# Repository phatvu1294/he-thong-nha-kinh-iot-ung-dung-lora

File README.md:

# Hệ thống nhà kính IO ứng dụng LoRa
*Hệ thống nhà kính IOT ứng dựng LoRa được phát triển dựa trên ESP32, Arduino, LoRa, MQTT, Nodejs và C# Winform*

### Giới thiệu
Đây là một dự án hoàn toàn mới tại Việt Nam, việc áp dụng IOT và công nghệ LoRa đã mở ra một bước đi mới trong nghành nông nghiệp. Đi đôi với cuộc cách mạng công nghệ 4.0, IOT là một phần thiết yếu để phát triển nông nghiệp. Với việc gần như được áp dụng vào thực tế, càng chứng tỏ đây chính là một dự án cấp thiết, việc nghiên cứu và phát triển thêm sẽ càng giúp cho đất nước chúng ta hội nhập và phát triển hơn nữa.

### Mô hình

Mô hình lấy Gateway làm trung tâm để xây dựng, Gateway được xây dựng bằng module ESP32, module LoRa Ra-01 và OLED, có nhiệm vụ là chờ tiếp nhận dữ liệu LoRa từ các Node cảm biến (Node CO2, Node Temp, Node Light), xử lý hiển thị OLED và publish chúng lên broker, sau đó được đẩy lên Server hoặc phần mềm điều khiển (C# Winform).

Node cảm biển, cụ thể ở đây là Node CO2 được xây dựng bằng vi điều khiển ATMega328, module LoRa Ra-01, OLED và cảm biến COZIR-AX-5000. Nhiệm vụ là đọc giá trị CO2 và truyền dữ liệu LoRa tới Gateway.

Gateway kết nối với Server hoặc phần mềm thông qua phương thức MQTT, đây là phương thức truyền nhanh, với tốc độ băng thông thấp, … Chúng có dạng publish/subscribe. Khi nhận được dữ liệu LoRa từ Node cảm biến. Gateway xử lý dữ liệu và publish lên broker một message thông qua một topic, lúc này Server hoặc phần mềm sẽ subscribe topic đó và lắng nghe liên tục message từ topic đó, chỉ cần có một dữ liệu gửi lên từ Gateway, lập tức Server và phần mềm sẽ cập nhật giá trị mới theo message đã nhận được, ngược lại, khi Server hoặc Gateway publish dữ liệu, Gateway sẽ subscribe và lắng nghe chúng, nếu có message gửi về từ Server hoặc phần mềm, lập tức Gateway nhận được và chuyển thành dữ liệu LoRa và truyền đi tức thời tới Node điều khiển (Node Relay).

Server được xây dựng trên nền tảng Node.js và phần mềm được xây dựng trên nền tảng C# .NET. Tất cả chúng đều đã có thư viện MQTT hỗ trợ, việc còn lại là do người lập trình sáng tạo chúng như thế nào mà thôi.

### Gateway

Gateway được xây dựng với hạt nhân là module ESP32 và module LoRa Ra-01. Module ESP32 sử dụng chip 32 bit lõi kép cho phép xử lý dữ liệu tốc độ cao, ổn định. Module LoRa Ra-01 sử dụng chip SX1278 hỗ trợ truyền không dây RF lên tận hàng Km.

### Node CO2

Node CO2 được xây dựng với vđk ATMega328 (Arduino), module LoRa Ra-01 và cảm biến COZIR-AX-5000. Cảm biến COZIR là cảm biến số cho phép đọc giá trị CO2 trực tiếp thông qua UART mà không cần phải tính toán gì nhiều.

### Server Nodejs

Server được xây dựng dựa trên nền tảng Node.js. Với việc sử dụng Socket.io cho phép Server hoạt động thời gian thực. Hệ thống đưa ra khuyến nghị ứng với từng giá trị. Ngoài ra còn có trang dự báo thời tiết cho phép xem tình hình thời tiết trong những ngày sắp tới.

### Phần mềm Winform

Phần mềm được xây dựng dựa trên nền tảng C# .NET. Hỗ trợ nhật ký cho phép người sử dụng theo dõi được sự thay đổi tức thời của các giá trị.

### Video demo hệ thống

[https://www.youtube.com/watch?v=TktAAO-llQs](https://www.youtube.com/watch?v=TktAAO-llQs)

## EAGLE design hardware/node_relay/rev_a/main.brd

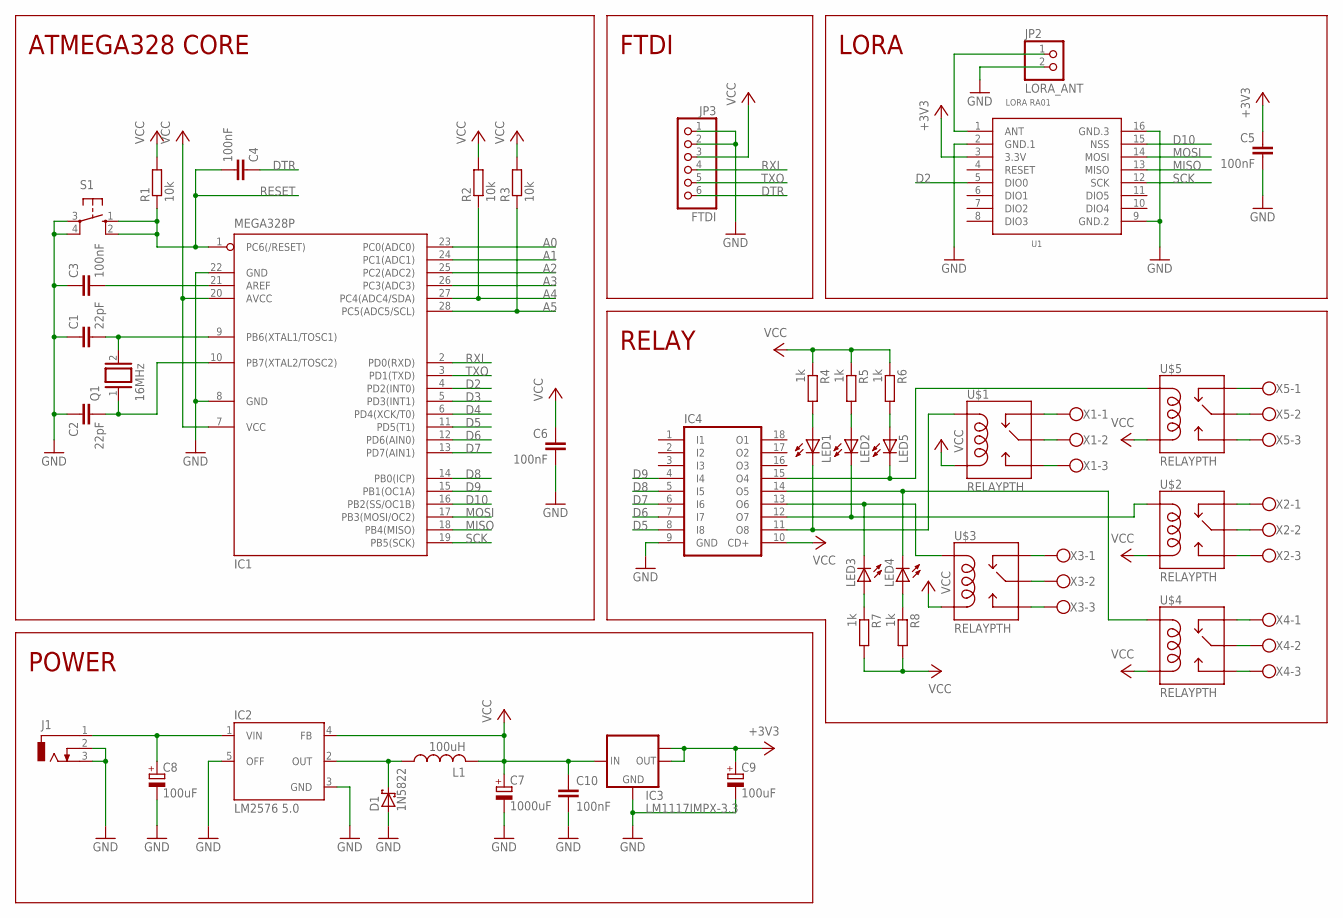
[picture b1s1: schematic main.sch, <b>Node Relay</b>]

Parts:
C1, C2: 22pF; C050-024X044
C3, C4, C5, C6, C10: 100nF; C050-024X044
C7: 1000uF; E5-13
C8: 100uF; E5-8,5
C9: 100uF; E3,5-10
D1: 1N5822; DO201T15
IC1: MEGA328P; DIL28-3
IC2: LM2576 5.0; TO263-5
IC3: LM1117IMPX-3.3; SOT223
IC4: ULN2803A; DIL18
J1: DCJ0303
JP2: LORA_ANT; 1X02
JP3: FTDI; 1X06
L1: 100uH; 6000-XXXX-RC
LED1, LED2, LED3, LED4, LED5: LED3MM
Q1: 16MHz; QS
R1, R2, R3: 10k; 0207/10
R4, R5, R6, R7, R8: 1k; 0207/10
S1: 10-XX; B3F-10XX
U1: LORA RA01; LORA-RA1-SMD
U$1, U$2, U$3, U$4, U$5: RELAYPTH; SRD-05VDC-SL-C
X1, X2, X3, X4, X5: W237-103

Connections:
+3V3: C5.1, C9.+, IC3.2 (OUT), IC3.TAB (OUT1), U1.3 (3.3V)
A0: IC1.23 (PC0(ADC0))
A1: IC1.24 (PC1(ADC1))
A2: IC1.25 (PC2(ADC2))
A3: IC1.26 (PC3(ADC3))
A4: IC1.27 (PC4(ADC4/SDA)), R2.1
A5: IC1.28 (PC5(ADC5/SCL)), R3.1
D2: IC1.4 (PD2(INT0)), U1.5 (DIO0)
D3: IC1.5 (PD3(INT1))
D4: IC1.6 (PD4(XCK/T0))
D5: IC1.11 (PD5(T1)), IC4.8 (I8)
D6: IC1.12 (PD6(AIN0)), IC4.7 (I7)
D7: IC1.13 (PD7(AIN1)), IC4.6 (I6)
D8: IC1.14 (PB0(ICP)), IC4.5 (I5)
D9: IC1.15 (PB1(OC1A)), IC4.4 (I4)
D10: IC1.16 (PB2(SS/OC1B)), U1.15 (NSS)
DTR: C4.1, JP3.6
GND: C1.1, C2.1, C3.1, C5.2, C6.2, C7.-, C8.-, C9.-, C10.2, D1.A, IC1.8 (GND), IC1.22 (GND), IC2.3 (GND), IC2.5 (OFF), IC3.1 (GND), IC4.9 (GND), J1.2, J1.3, JP2.2, JP3.1, JP3.2, S1.3, S1.4 (P1), U1.2 (GND.1), U1.9 (GND.2), U1.16 (GND.3)
MISO: IC1.18 (PB4(MISO)), U1.13 (MISO)
MOSI: IC1.17 (PB3(MOSI/OC2)), U1.14 (MOSI)
unnamed: JP2.1, U1.1 (ANT)
unnamed: C1.2, IC1.9 (PB6(XTAL1/TOSC1)), Q1.2
unnamed: C2.2, IC1.10 (PB7(XTAL2/TOSC2)), Q1.1
unnamed: C3.2, IC1.21 (AREF)
unnamed: C8.+, IC2.1 (VIN), J1.1
unnamed: D1.C, IC2.2 (OUT), L1.1
unnamed: U$1.SWCLOSED (SWCLOSE), X1.1
unnamed: U$1.SWCOMMON, X1.2
unnamed: U$1.SWOPEN, X1.3
unnamed: U$3.SWCOMMON, X3.2
unnamed: U$3.SWCLOSED (SWCLOSE), X3.1
unnamed: U$3.SWOPEN, X3.3
unnamed: U$4.SWCLOSED (SWCLOSE), X4.1
unnamed: U$4.SWCOMMON, X4.2
unnamed: U$4.SWOPEN, X4.3
unnamed: U$2.SWOPEN, X2.3
unnamed: U$2.SWCLOSED (SWCLOSE), X2.1
unnamed: U$2.SWCOMMON, X2.2
unnamed: IC4.11 (O8), LED1.K (C), U$1.COIL1
unnamed: IC4.12 (O7), LED2.K (C), U$2.COIL1
unnamed: IC4.13 (O6), LED3.K (C), U$3.COIL1
unnamed: IC4.14 (O5), LED4.K (C), U$4.COIL1
unnamed: U$5.SWCLOSED (SWCLOSE), X5.1
unnamed: U$5.SWOPEN, X5.3
unnamed: U$5.SWCOMMON, X5.2
unnamed: IC4.15 (O4), LED5.K (C), U$5.COIL1
unnamed: LED1.A, R4.2
unnamed: LED2.A, R5.2
unnamed: LED5.A, R6.2
unnamed: LED3.A, R7.1
unnamed: LED4.A, R8.1
RESET: C4.2, IC1.1 (PC6(/RESET)), R1.1, S1.1 (S), S1.2 (S1)
RXI: IC1.2 (PD0(RXD)), JP3.4
SCK: IC1.19 (PB5(SCK)), U1.12 (SCK)
TXO: IC1.3 (PD1(TXD)), JP3.5
VCC: C6.1, C7.+, C10.1, IC1.7 (VCC), IC1.20 (AVCC), IC2.4 (FB), IC3.3 (IN), IC4.10 (CD+), JP3.3, L1.2, R1.2, R2.2, R3.2, R4.1, R5.1, R6.1, R7.2, R8.2, U$1.COIL0, U$2.COIL0, U$3.COIL0, U$4.COIL0, U$5.COIL0

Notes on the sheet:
LORA
ATMEGA328 CORE
FTDI
POWER
RELAY

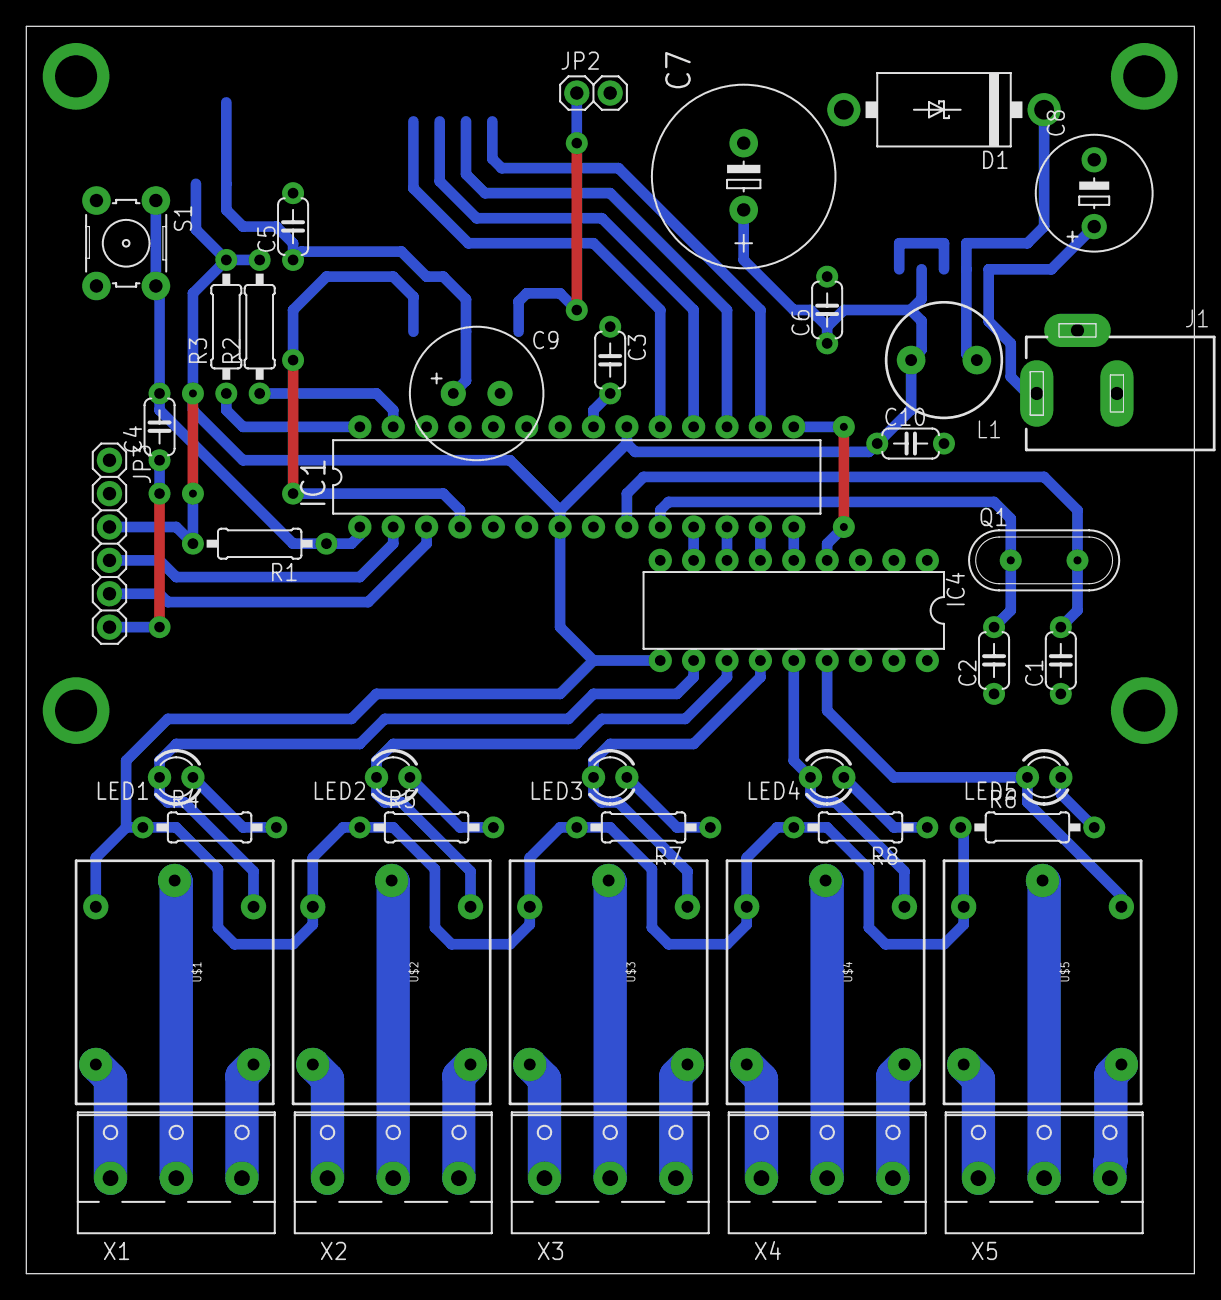
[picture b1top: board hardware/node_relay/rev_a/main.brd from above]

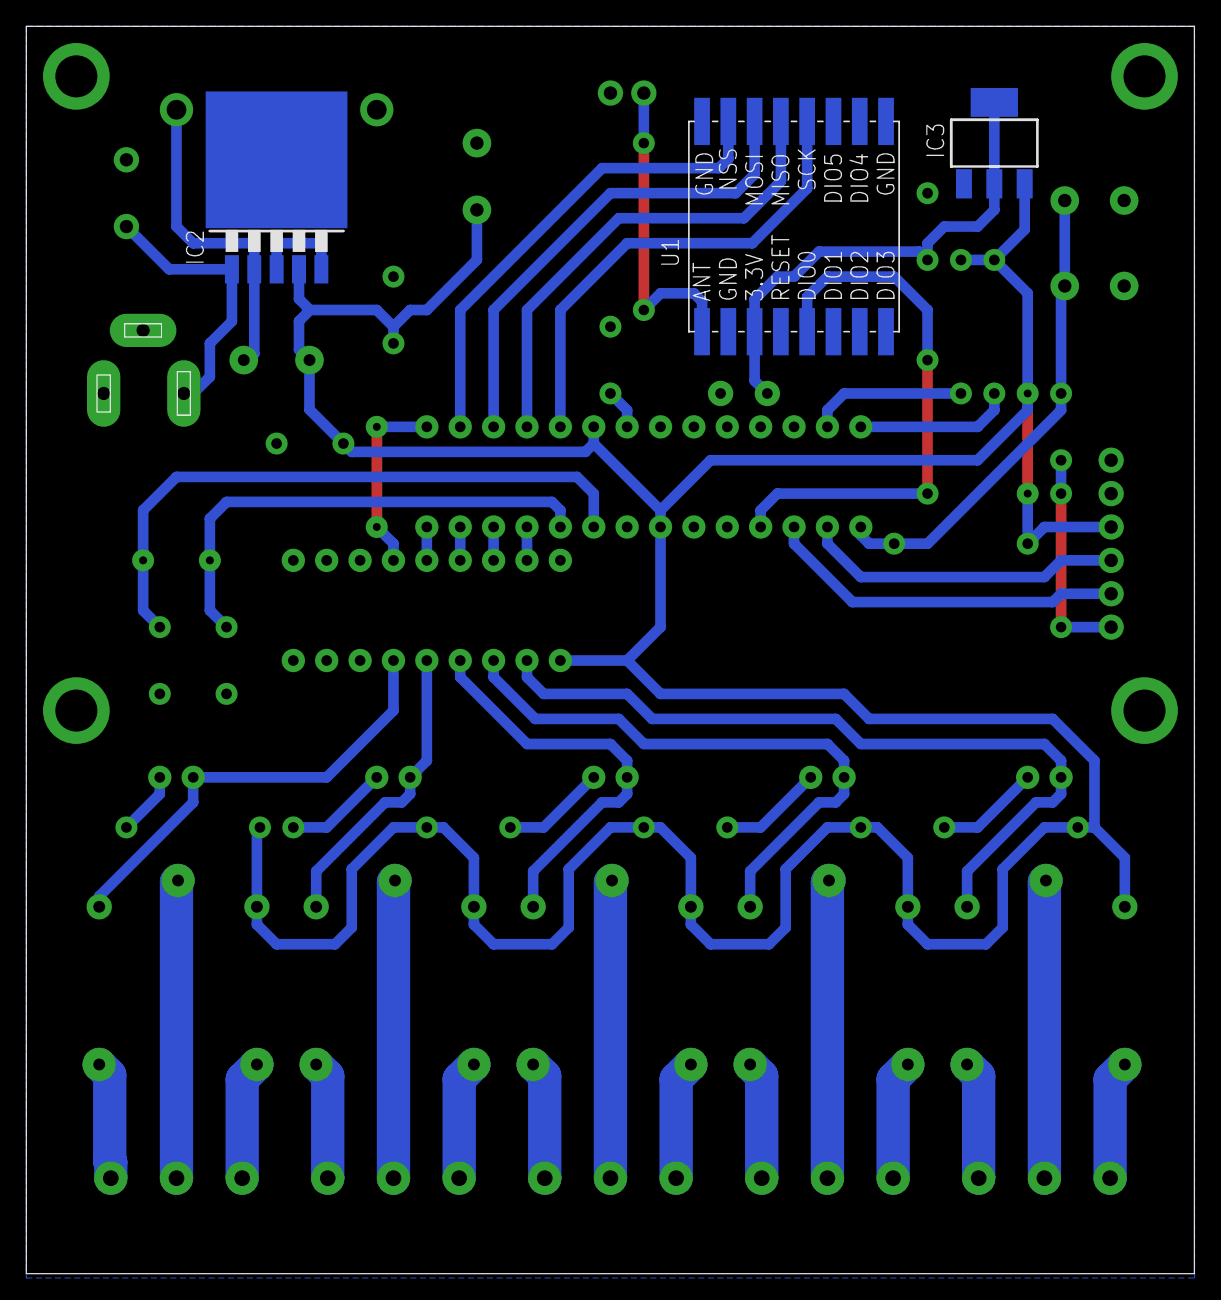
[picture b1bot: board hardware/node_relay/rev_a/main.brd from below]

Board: 2 copper layers, 88.9 x 94.9 mm, 45 parts (3 on the bottom side), 50 nets.

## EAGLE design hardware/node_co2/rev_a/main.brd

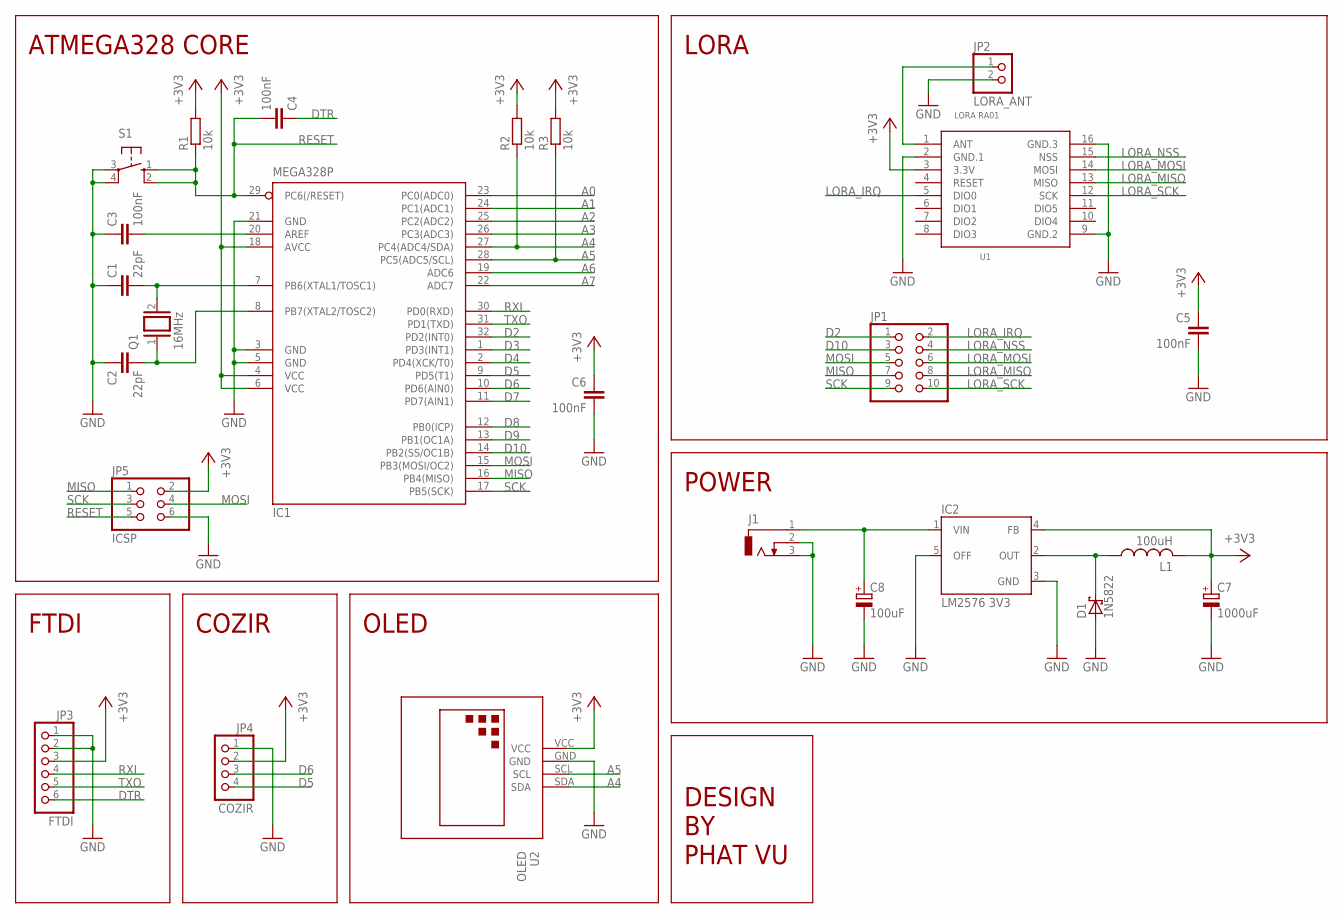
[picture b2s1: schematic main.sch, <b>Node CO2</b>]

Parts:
C1, C2: 22pF; C050-024X044
C3, C4, C5, C6: 100nF; C050-024X044
C7: 1000uF; E5-13
C8: 100uF; E5-8,5
D1: 1N5822; DO201T15
IC1: MEGA328P; TQFP32-08
IC2: LM2576 3V3; TO263-5
J1: DCJ0303
JP1: PINHD-2X5; 2X05
JP2: LORA_ANT; 1X02
JP3: FTDI; 1X06
JP4: COZIR; 1X04
JP5: ICSP; 2X03
L1: 100uH; 6000-XXXX-RC
Q1: 16MHz; QS
R1, R2, R3: 10k; 0207/10
S1: 10-XX; B3F-10XX
U1: LORA RA01; LORA-RA1-SMD
U2: OLED; OLED-096-I2C

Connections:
+3V3: C5.1, C6.1, C7.+, IC1.4 (VCC), IC1.6 (VCC), IC1.18 (AVCC), IC2.4 (FB), JP3.3, JP4.2, JP5.2, L1.2, R1.2, R2.2, R3.2, U1.3 (3.3V), U2.VCC
A0: IC1.23 (PC0(ADC0))
A1: IC1.24 (PC1(ADC1))
A2: IC1.25 (PC2(ADC2))
A3: IC1.26 (PC3(ADC3))
A4: IC1.27 (PC4(ADC4/SDA)), R2.1, U2.SDA
A5: IC1.28 (PC5(ADC5/SCL)), R3.1, U2.SCL
A6: IC1.19 (ADC6)
A7: IC1.22 (ADC7)
D2: IC1.32 (PD2(INT0)), JP1.1
D3: IC1.1 (PD3(INT1))
D4: IC1.2 (PD4(XCK/T0))
D5: IC1.9 (PD5(T1)), JP4.4
D6: IC1.10 (PD6(AIN0)), JP4.3
D7: IC1.11 (PD7(AIN1))
D8: IC1.12 (PB0(ICP))
D9: IC1.13 (PB1(OC1A))
D10: IC1.14 (PB2(SS/OC1B)), JP1.3
DTR: C4.1, JP3.6
GND: C1.1, C2.1, C3.1, C5.2, C6.2, C7.-, C8.-, D1.A, IC1.3 (GND), IC1.5 (GND), IC1.21 (GND), IC2.3 (GND), IC2.5 (OFF), J1.2, J1.3, JP2.2, JP3.1, JP3.2, JP4.1, JP5.6, S1.3, S1.4 (P1), U1.2 (GND.1), U1.9 (GND.2), U1.16 (GND.3), U2.GND
LORA_IRQ: JP1.2, U1.5 (DIO0)
LORA_MISO: JP1.8, U1.13 (MISO)
LORA_MOSI: JP1.6, U1.14 (MOSI)
LORA_NSS: JP1.4, U1.15 (NSS)
LORA_SCK: JP1.10, U1.12 (SCK)
MISO: IC1.16 (PB4(MISO)), JP1.7, JP5.1
MOSI: IC1.15 (PB3(MOSI/OC2)), JP1.5, JP5.4
unnamed: JP2.1, U1.1 (ANT)
unnamed: C1.2, IC1.7 (PB6(XTAL1/TOSC1)), Q1.2
unnamed: C2.2, IC1.8 (PB7(XTAL2/TOSC2)), Q1.1
unnamed: C3.2, IC1.20 (AREF)
unnamed: C8.+, IC2.1 (VIN), J1.1
unnamed: D1.C, IC2.2 (OUT), L1.1
RESET: C4.2, IC1.29 (PC6(/RESET)), JP5.5, R1.1, S1.1 (S), S1.2 (S1)
RXI: IC1.30 (PD0(RXD)), JP3.4
SCK: IC1.17 (PB5(SCK)), JP1.9, JP5.3
TXO: IC1.31 (PD1(TXD)), JP3.5

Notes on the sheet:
LORA
ATMEGA328 CORE
FTDI
COZIR
OLED
POWER
DESIGN BY PHAT VU

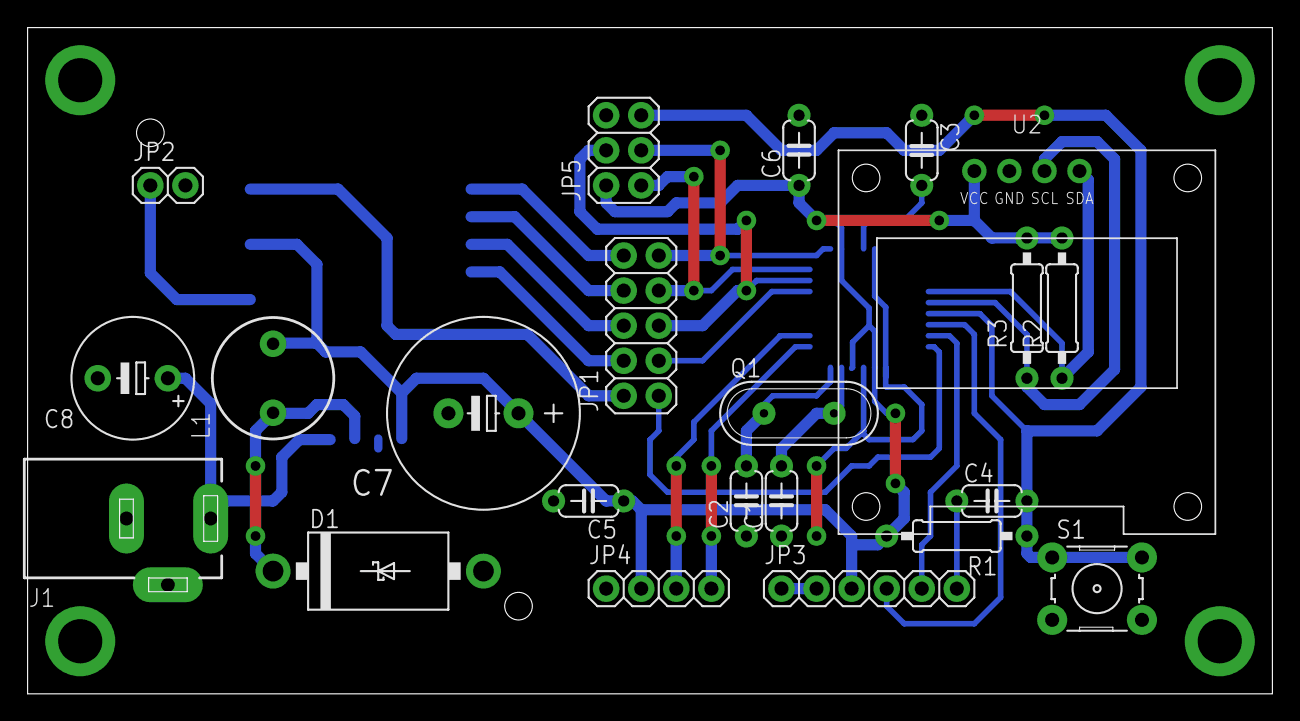
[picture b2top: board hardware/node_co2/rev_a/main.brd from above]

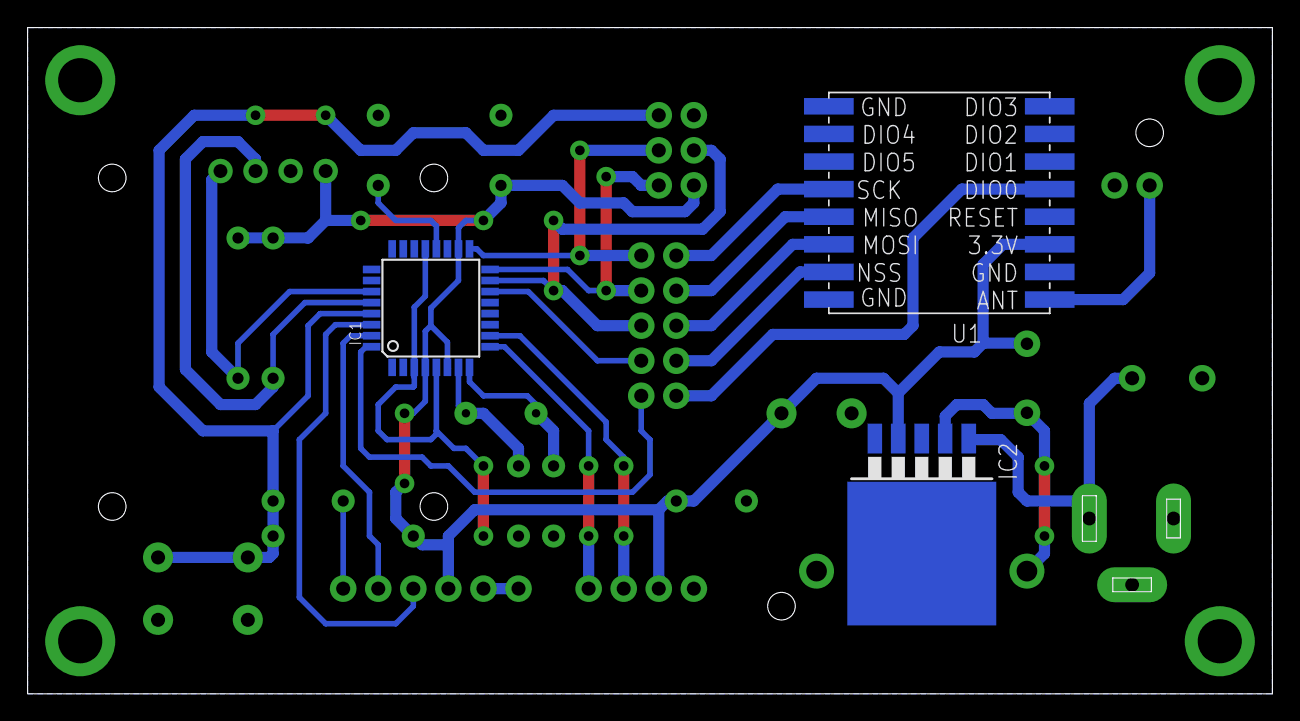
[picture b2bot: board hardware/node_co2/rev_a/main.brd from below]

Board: 2 copper layers, 90.2 x 48.3 mm, 25 parts (3 on the bottom side), 26 nets.

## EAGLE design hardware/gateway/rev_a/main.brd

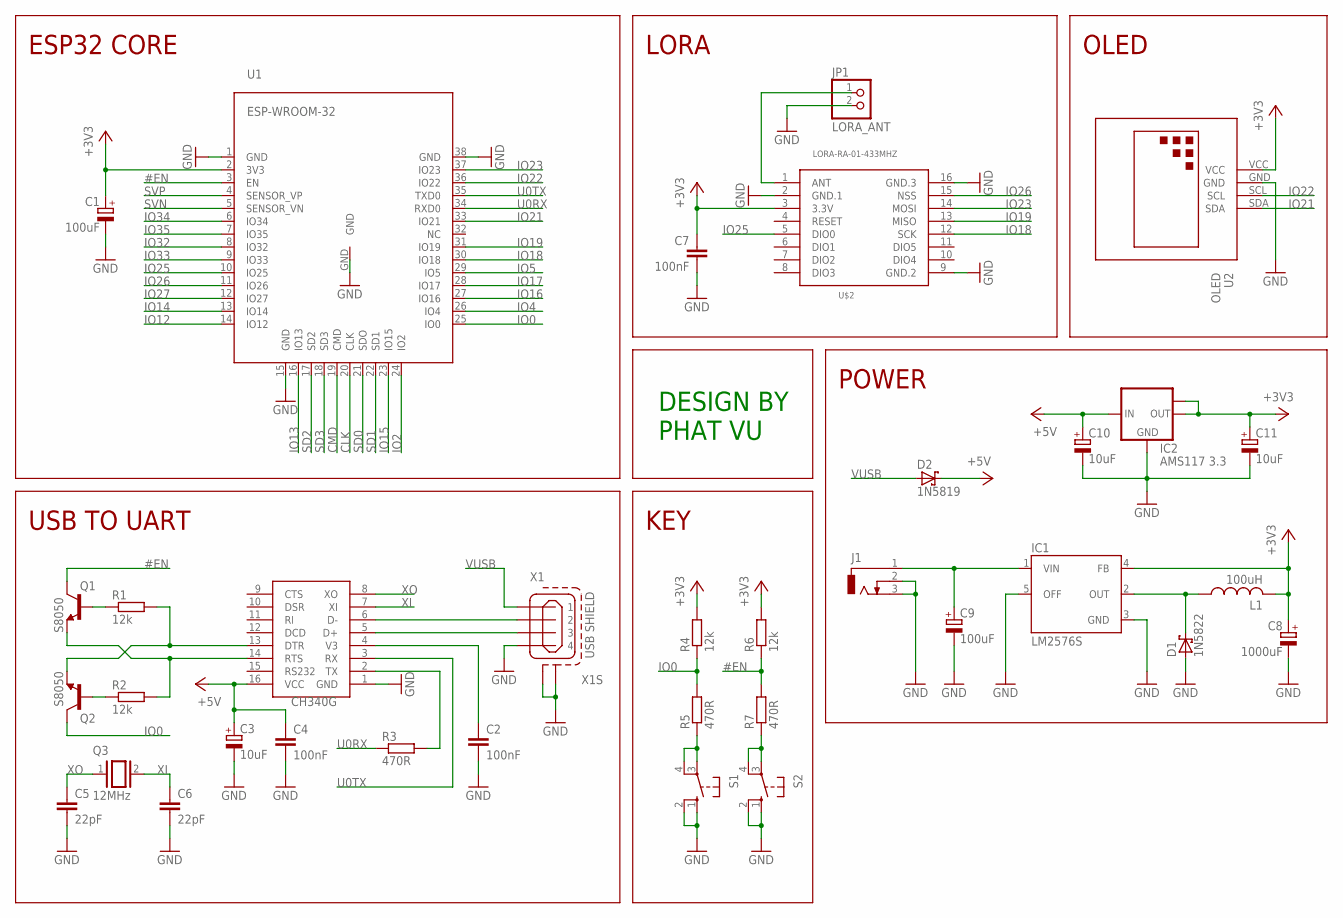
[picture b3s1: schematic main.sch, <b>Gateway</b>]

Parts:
C1, C9: 100uF; E5-10,5
C2, C4, C7: 100nF; C050-024X044
C3, C10, C11: 10uF; E2,5-6
C5, C6: 22pF; C050-024X044
C8: 1000uF; E5-13
D1: 1N5822; DO201T15
D2: 1N5819; DO41-7.6
IC1: LM2576S; TO263-5
IC2: AMS117 3.3; SOT223
J1: DCJ0303
JP1: LORA_ANT; 1X02
L1: 100uH; 6000-XXXX-RC
Q1, Q2: S8050; TO92-EBC
Q3: 12MHz; QS
R1, R2, R4, R6: 12k; 0207/10
R3, R5, R7: 470R; 0207/10
S1, S2: 10-XX; B3F-10XX
U1: ESP-WROOM-32
U2: OLED; OLED-096-I2C
U$1: CH340G; SOIC16
U$2: LORA-RA-01-433MHZ; LORA-RA1-SMD
X1: USB SHIELD; 85-32004-00X

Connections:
#EN: Q1.C, R6.1, R7.2, U1.3 (EN)
+3V3: C1.+, C7.1, C8.+, C11.+, IC1.4 (FB), IC2.2 (OUT), IC2.TAB (OUT1), L1.2, R4.2, R6.2, U1.2 (3V3), U2.VCC, U$2.3 (3.3V)
+5V: C3.+, C4.1, C10.+, D2.C, IC2.3 (IN), U$1.16 (VCC)
CLK: U1.20 (CLK)
CMD: U1.19 (CMD)
GND: C1.-, C2.2, C3.-, C4.2, C5.2, C6.2, C7.2, C8.-, C9.-, C10.-, C11.-, D1.A, IC1.3 (GND), IC1.5 (OFF), IC2.1 (GND), J1.2, J1.3, JP1.2, S1.1 (S), S1.2 (S1), S2.1 (S), S2.2 (S1), U1.1 (GND), U1.15 (GND), U1.38 (GND), U1.GND, U2.GND, U$1.1 (GND), U$2.2 (GND.1), U$2.9 (GND.2), U$2.16 (GND.3), X1.4, X1.M1 (S1), X1.M2 (S2)
IO0: Q2.C, R4.1, R5.2, U1.25 (IO0)
IO2: U1.24 (IO2)
IO4: U1.26 (IO4)
IO5: U1.29 (IO5)
IO12: U1.14 (IO12)
IO13: U1.16 (IO13)
IO14: U1.13 (IO14)
IO15: U1.23 (IO15)
IO16: U1.27 (IO16)
IO17: U1.28 (IO17)
IO18: U1.30 (IO18), U$2.12 (SCK)
IO19: U1.31 (IO19), U$2.13 (MISO)
IO21: U1.33 (IO21), U2.SDA
IO22: U1.36 (IO22), U2.SCL
IO23: U1.37 (IO23), U$2.14 (MOSI)
IO25: U1.10 (IO25), U$2.5 (DIO0)
IO26: U1.11 (IO26), U$2.15 (NSS)
IO27: U1.12 (IO27)
IO32: U1.8 (IO32)
IO33: U1.9 (IO33)
IO34: U1.6 (IO34)
IO35: U1.7 (IO35)
unnamed: JP1.1, U$2.1 (ANT)
unnamed: R3.2, U$1.2 (TX)
unnamed: U$1.6 (D-), X1.2
unnamed: U$1.5 (D+), X1.3
unnamed: C2.1, U$1.4 (V3)
unnamed: Q1.E, R2.2, U$1.14 (RTS)
unnamed: Q2.E, R1.2, U$1.13 (DTR)
unnamed: C9.+, IC1.1 (VIN), J1.1
unnamed: Q2.B, R2.1
unnamed: Q1.B, R1.1
unnamed: R7.1, S2.3, S2.4 (P1)
unnamed: R5.1, S1.3, S1.4 (P1)
unnamed: D1.C, IC1.2 (OUT), L1.1
SD0: U1.21 (SDO)
SD1: U1.22 (SD1)
SD2: U1.17 (SD2)
SD3: U1.18 (SD3)
SVN: U1.5 (SENSOR_VN)
SVP: U1.4 (SENSOR_VP)
U0RX: R3.1, U1.34 (RXD0)
U0TX: U1.35 (TXD0), U$1.3 (RX)
VUSB: D2.A, X1.1
XI: C6.1, Q3.2, U$1.7 (XI)
XO: C5.1, Q3.1, U$1.8 (XO)

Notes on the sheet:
ESP32 CORE
USB TO UART
KEY
LORA
OLED
POWER
DESIGN BY PHAT VU

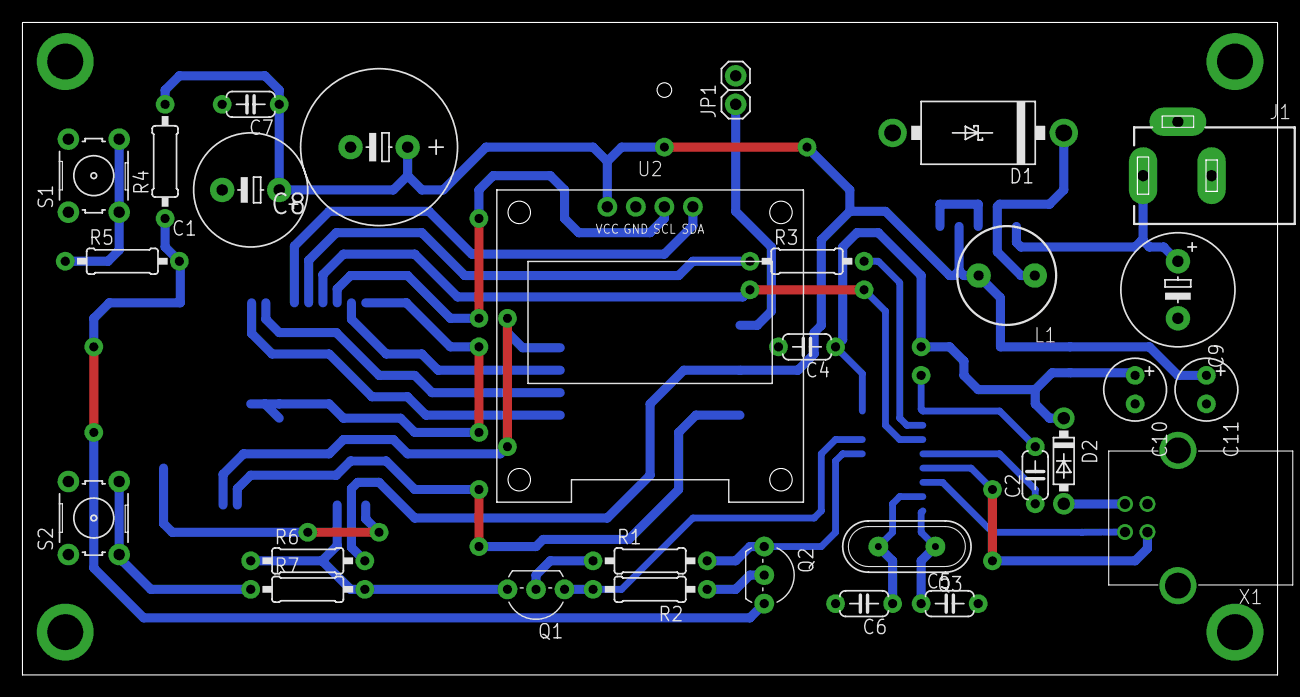
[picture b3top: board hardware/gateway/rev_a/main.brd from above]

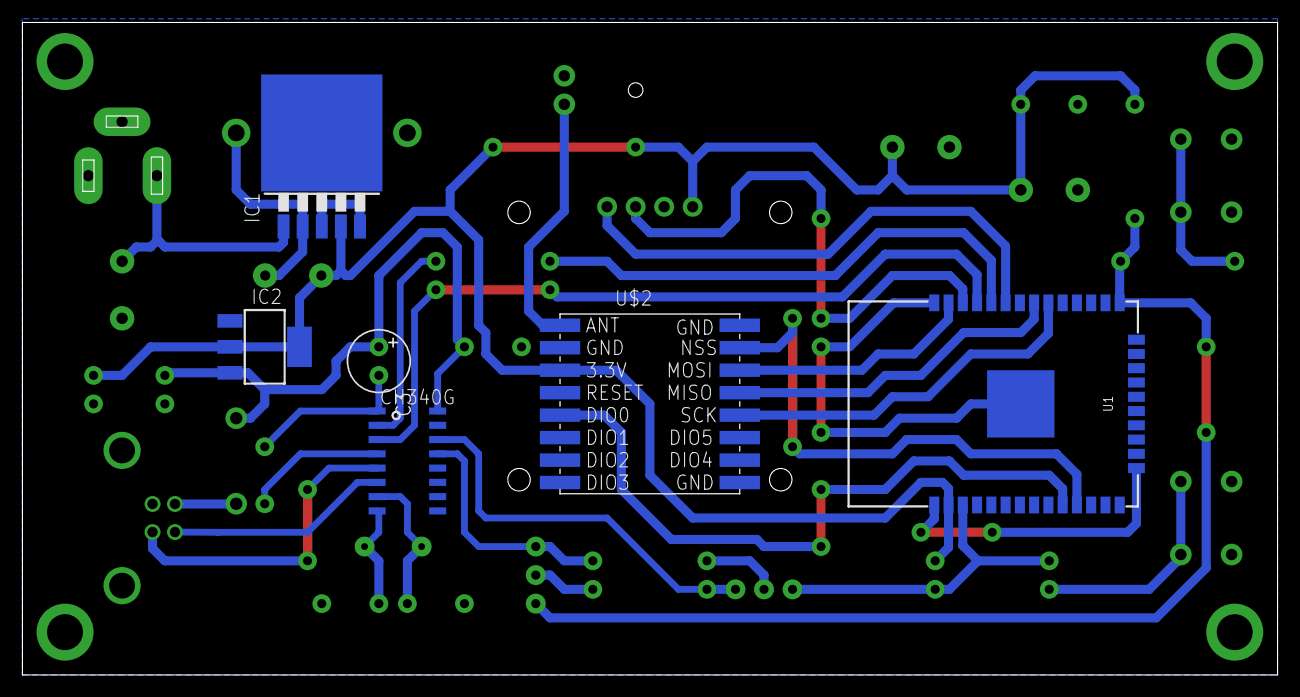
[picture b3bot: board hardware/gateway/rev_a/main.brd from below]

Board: 2 copper layers, 111.7 x 58.1 mm, 35 parts (6 on the bottom side), 30 nets.

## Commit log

2021-04-05 upload source
2021-04-05 sửa readme.md
2021-04-05 upload soure
